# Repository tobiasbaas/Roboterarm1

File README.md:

# Konzeption und Realisierung eines Edge-KI-Systems zur visuellen Posenschätzung eines Roboterarms

Herzlich willkommen zum Repo des Robotersarmes der Arbeitsgruppe. Bitte beachtet, dass es sich hierbei handelt 
um eine Erweiterung bereits vorhandener Infrastruktur. Für mehr Infos siehe das bisherige Github Repo:
- (https://github.com/mama1120/rpi_ros_can_module.git)

Sowie als auch das offiziele Wiki zu den vergangegen Projekten im Ilias:
- (https://ilias.h-ka.de/goto.php?target=wiki_787531#il_mhead_t_focus)

<br>

>In dieser Readme wird der Gesamte Aufbau des Roboterarmes inklusive der Erweiterung, die im Rahmen der 
>Bachelorthesis durchgeführt wurden, erläutert. Es soll einen Schnelleinstieg ermöglichen, indem ihr den 
>Roboter mithilfe des RaspberryPI, STM32N6 Board und eurem Laptop bewegen könnt. Für tieferes Verständis
>des Projektes navigiert in die Unterordner des Repo.

---

## 1. Systemübersicht

Drei Geräte arbeiten zusammen. Der Laptop ist der Taktgeber, er steuert den Roboter und
löst die Bildaufnahme aus.

```
        ┌──────────────────────────────┐
        │  Laptop (Windows)            │
        │  capture_image.py            │
        └───────┬──────────────┬───────┘
                │              │
   UDP (WLAN)   │              │  USB CDC (virtueller COM-Port)
   4x float32   │              │  Kommandos: PING / TEST / CAPTURE
   Winkel [rad] │              │  Antwort: Bild 640x480 RGB565
                ▼              ▼
   ┌───────────────────┐   ┌──────────────────────────┐
   │ Raspberry Pi      │   │ STM32N6570-DK            │
   │ ROS2 + UDP-Bridge │   │ Kamera IMX335 + NPU      │
   │ CAN-Bus           │   │ Live-Bild auf LCD        │
   └────────┬──────────┘   └──────────────────────────┘
            │ CAN
            ▼
     ┌──────────────┐
     │ Roboterarm   │   Open-Loop, 4 Gelenke, keine Encoder
     └──────────────┘
```

**Warum dieser Aufbau?**
Der Roboterarm ist ein Open-Loop-System, es gibt keine Rotary-Encoder oder Hallsensoren,
die den tatsächlichen Winkel zurückmelden. Für das KI-Training muss aber jedes Bild exakt
zu einem bekannten Winkelsatz gehören. Deshalb wird der Roboter nicht über RViz von Hand
bewegt, sondern von einem eigenen Python-Skript auf eine bekannte Zielpose gefahren.
Das Skript wartet, bis die Bewegung sicher abgeschlossen ist, löst dann die Bildaufnahme
aus und schreibt Bild und Winkel gemeinsam in eine CSV-Datei. Eine korrekt angefahrene
Nullposition ist dabei die Grundvoraussetzung.

---

## 2. Repository-Struktur

```
.
├── 02_Software/
│   ├── Beachlor_Thesis_AI/     # KI-Pipeline (Training, Datenaufbereitung, Export)
│   ├── Image_Capture_Python/   # Host-Skripte: Trainingsdatenaufnahme (nur zusammen mit STM)
│   ├── New_Image_Capture/      # STM32-Firmware: Trainingsdatenaufnahme (Echte Bilder)
│   └── Thesis_Robot_Pose/      # STM32-Firmware: zusätzlich KI-Inferenz auf der NPU
├── 03_Hardware/
│   ├── STM32N6_Thesis_Board/   # Eigenes KiCad-Board (STM32N657X0H3Q)
│   └── Nucleo_PCB_FIles/       # Altium-Daten des MB1940-Referenzdesigns
└── README.md                   # diese Datei
```

## 3. Schellstart

### 3.1 Voraussetzungen

**Hardware**

| Komponente | Anmerkung |
|---|---|
| Roboterarm mit CAN-Anbindung | 4 angesteuerte Gelenke |
| Raspberry Pi | ROS2 im Docker-Image, CAN-HAT |
| STM32N6570-DK | Kamera IMX335, LCD RK050HR18 |
| Laptop | Windows, MAC |

> [!IMPORTANT]
>Bittet achtet darauf, dass euer Laptop und der Raspberry im selben Netzwerk miteinander verbunden sind!

<br>

**Software auf dem Laptop**

Falls ihr noch kein Python auf euren Laptop verwendet habt, so installiert zuerst **Miniconda**
(https://www.anaconda.com/download/success) und erstellt ein Custom Environment für 
dieses Projekt. 

Dazu öffnet ihr das **Anaconda Powershell** und gibt folgenden Commands **nacheinander**
in das Terminal ein:

```bash
conda create --name Euer_Env_Name python=3.14
```

```bash
conda activate Euer_Env_Name
```

```bash
pip install ultralytics==8.4.146 torch==2.14.0 onnx==1.22.0 onnxruntime==1.29.0 opencv-python==5.0.0.93 numpy==2.4.6 pillow==12.3.0 pandas==3.0.5 matplotlib==3.11.1 pyserial==3.5 notebook==7.6.2 label-studio==1.23.0
```

Zusätzlich benötigt ihr für die Inbetriebnahme des STM32N6 Boards die folgende Software 
von ST-Microelectronics:

- STM32 VsCode Extension  (https://www.st.com/content/st_com/en/campaigns/stm32-vs-code-extension-z11.html)
- STM32 Cube CLT          (https://www.st.com/en/development-tools/stm32cubeclt.html)
- STM32 Cube Programmer   (https://www.st.com/en/development-tools/stm32cubeprog.html)
- STM32Cube AI Studio     (https://www.st.com/content/st_com/en/campaigns/edge-ai-toolchain-for-mcus-z14.html)

### 3.2 Schritt 1: Roboter am Raspberry Pi starten

> [!IMPORTANT]
> Das **Passwort** für den Pi selber und der Ausführung des Codes lautet: **`ubuntu`**.

Auf dem Raspberry Pi genügt **ein Terminal und ein Befehl**. Alle Docker-Workspaces
werden dabei im Hintergrund initialisiert:

```bash
./boot_robot.sh
```

Damit werden gestartet:

* CAN-Bus
* ROS2 inklusive aktiver UDP-Bridge
  
Nachdem alles initialisiert hat, kann der Roboter bereits gesteuert werden über RViz. Für mehr Infos zum 
starten von RViz, schaut im oben verlinkten GitHub Repo nach.<br>

Optional, um die CAN-Nachrichten live mitzulesen (zweites Terminal, erst nach dem
Start des Roboters):

```bash
candump can0
```
> [!IMPORTANT]
> Den Roboter niemals gleichzeitig über RViz und über das Python-Skript
> ansprechen. 

### 3.3 Schritt 2: STM32N6570-DK vorbereiten

1. Boot-Pins **BOOT0 und BOOT1 auf Low** setzen (Flash-Mode, bevorzugte Betriebsart).
2. FSBL und Appli in der CubeIDE bauen.
3. Beide `.bin`-Dateien signieren, siehe [Abschnitt 4](#4-firmware-flashen-signierung).
4. External Flash löschen, dann **erst FSBL, danach Appli** flashen.
5. Board per USB an den Laptop stecken. Es meldet sich als virtueller COM-Port und sendet
   nach der Enumeration dreimal `READY`.

Für die reine Datenaufnahme wird `02_Software/New_Image_Capture` geflasht.

### 3.4 Schritt 3: Bildaufnahme starten

In `02_Software/Image_Capture_Python/capture_image.py` oben die Konfiguration prüfen:

```python
COM_PORT = "COM4"              # COM-Port des STM32 im Gerätemanager nachsehen
UDP_IP   = "192.168.4.152"     # IP des Raspberry Pi
UDP_PORT = 5005
num_positions = 1000           # Anzahl aufzunehmender Posen
```

Dann starten:

```bash
cd 02_Software/Image_Capture_Python
python capture_image.py
```

Ablauf pro Bild: Zielpose per UDP senden, 4 s warten, `CAPTURE` über USB senden,
Bild empfangen, als PNG speichern, Zeile in `labels.csv` schreiben.

Ergebnis liegt in `dataset/images/<lauf_zeitstempel>/pose_XXXX.png` plus `dataset/labels.csv`.

---

## 4. Firmware flashen: Signierung

Der STM32N6 führt nur signierte Images aus. FSBL und Appli müssen **getrennt** signiert
werden.
<br><br>

> [!IMPORTANT]
>Das Skript `sign_binaries.bat` im jeweiligen Firmware-Projekt automatisiert die folgenden Schritte.

<br>
1. In der CubeIDE beide Umgebungen bauen. Die `.bin` liegt im `Debug`-Ordner des jeweiligen
   Projekts.
2. Eingabeaufforderung öffnen und in dieses Verzeichnis wechseln:

   ```bat
   cd /d <Pfad zum Debug-Ordner>
   ```

3. Signieren:

   ```bat
   STM32_SigningTool_CLI.exe -bin <name>.bin -t fsbl -la 0x80000000 -hv 2.3 -nk -o <name>-trusted.bin -align -dump <name>-trusted.bin
   ```

   Das Ergebnis der Signierung steht **ganz oben** in der Ausgabe, nicht am Ende.
4. Die entstandene `*-trusted.bin` mit dem STM32CubeProgrammer flashen.
   Reihenfolge: External Flash löschen, dann FSBL, dann Appli.

---

## 5. Schnittstellen im Detail

### 5.1 Laptop zu Raspberry Pi (UDP)

| Eigenschaft | Wert |
|---|---|
| Protokoll | UDP, unidirektional (Laptop sendet) |
| Ziel | `192.168.4.152:5005` |
| Nutzdaten | 4 x `float32`, Big-Endian (`struct` Format `!4f`) |
| Einheit | **Radiant**, Reihenfolge Joint 1 bis Joint 4 |
| Gelenkgrenzen | J1 -95° bis 95°, J2 0° bis 95°, J3 -80° bis 80°, J4 -10° bis 50° |

Vor dem Start fährt das Skript dreimal die Nullposition `[0,0,0,0]` an und wartet 4 s.

**Änderung am Raspberry Pi:** Die UDP-Bridge wurde in
`robot_moveit_config/launch/planning_execution.launch.py` ergänzt. Die betroffenen Stellen
sind in der Datei markiert, weitere Anpassungen sind für Folgeprojekte nicht nötig.
Aktiviert wird sie über den Launch-Parameter:

```bash
ros2 launch robot_moveit_config planning_execution.launch.py use_udp_bridge:=true
```

`boot_robot.sh` setzt diesen Parameter bereits. Der normale ROS2-Workflow bleibt
unverändert, RViz funktioniert weiterhin (aber nicht gleichzeitig, siehe Warnung oben).

---

## 6. Troubleshooting

| Symptom | Ursache und Abhilfe |
|---|---|
| `capture_image.py` bleibt bei "Warte auf Lebenszeichen" | Board sendet kein `READY`. Board resetten, COM-Port im Gerätemanager prüfen, ggf. Firmware nicht korrekt geflasht |
| Roboter reagiert nicht auf UDP | `boot_robot.sh` gestartet? UDP-Bridge aktiv? Laptop und Pi im selben WLAN? IP in `capture_image.py` korrekt? |
| Roboter fährt ruckartig oder unvorhersehbar | RViz läuft parallel. Nur eine Steuerquelle gleichzeitig verwenden |
| Bilder und Winkel passen nicht zusammen | Nullposition nicht korrekt angefahren, oder Wartezeit nach der Bewegung zu kurz |
| Board startet nach dem Flashen nicht | Signierung fehlt oder falsche Reihenfolge. External Flash löschen, erst FSBL, dann Appli |
| Bild kommt unvollständig an | `CAPTURE_TIMEOUT` erhöhen, anderes USB-Kabel oder anderen Port verwenden |

---

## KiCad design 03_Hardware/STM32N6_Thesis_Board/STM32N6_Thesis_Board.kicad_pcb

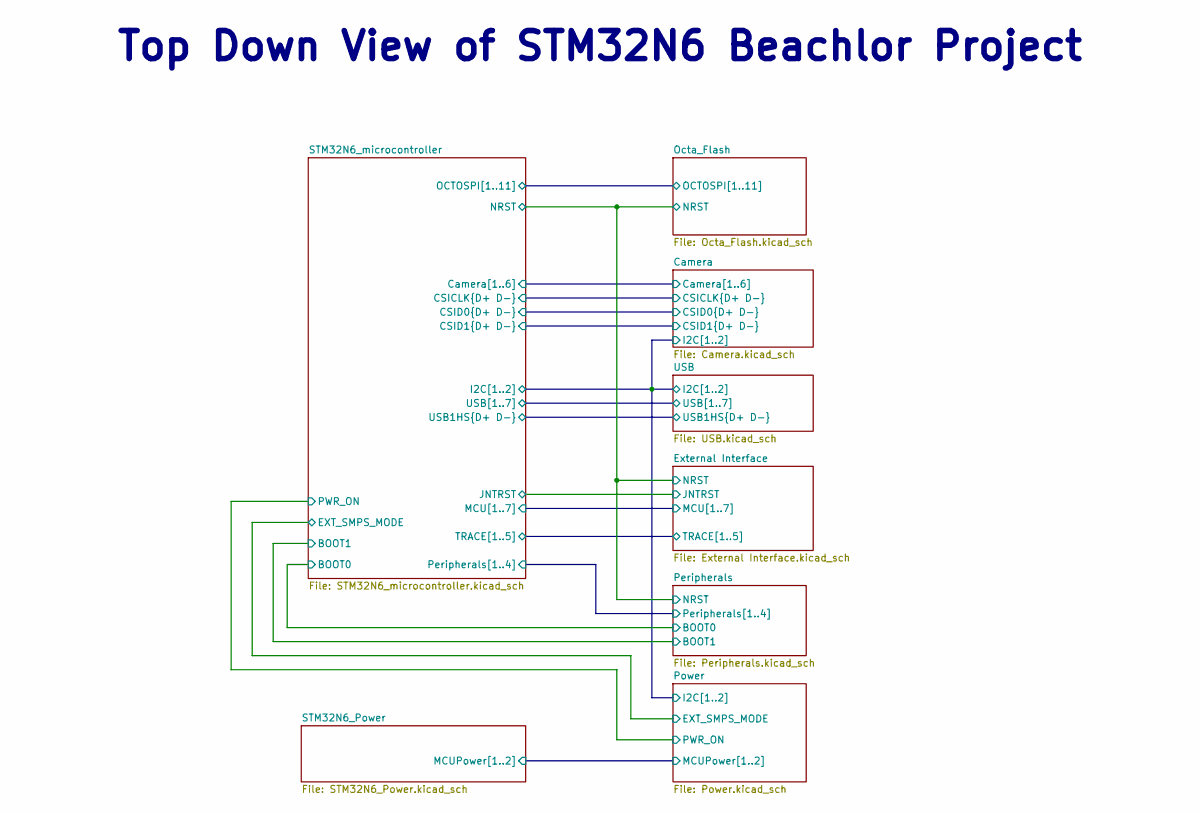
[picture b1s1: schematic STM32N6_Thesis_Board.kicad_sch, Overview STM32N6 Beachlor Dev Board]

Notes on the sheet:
Top Down View of STM32N6 Beachlor Project

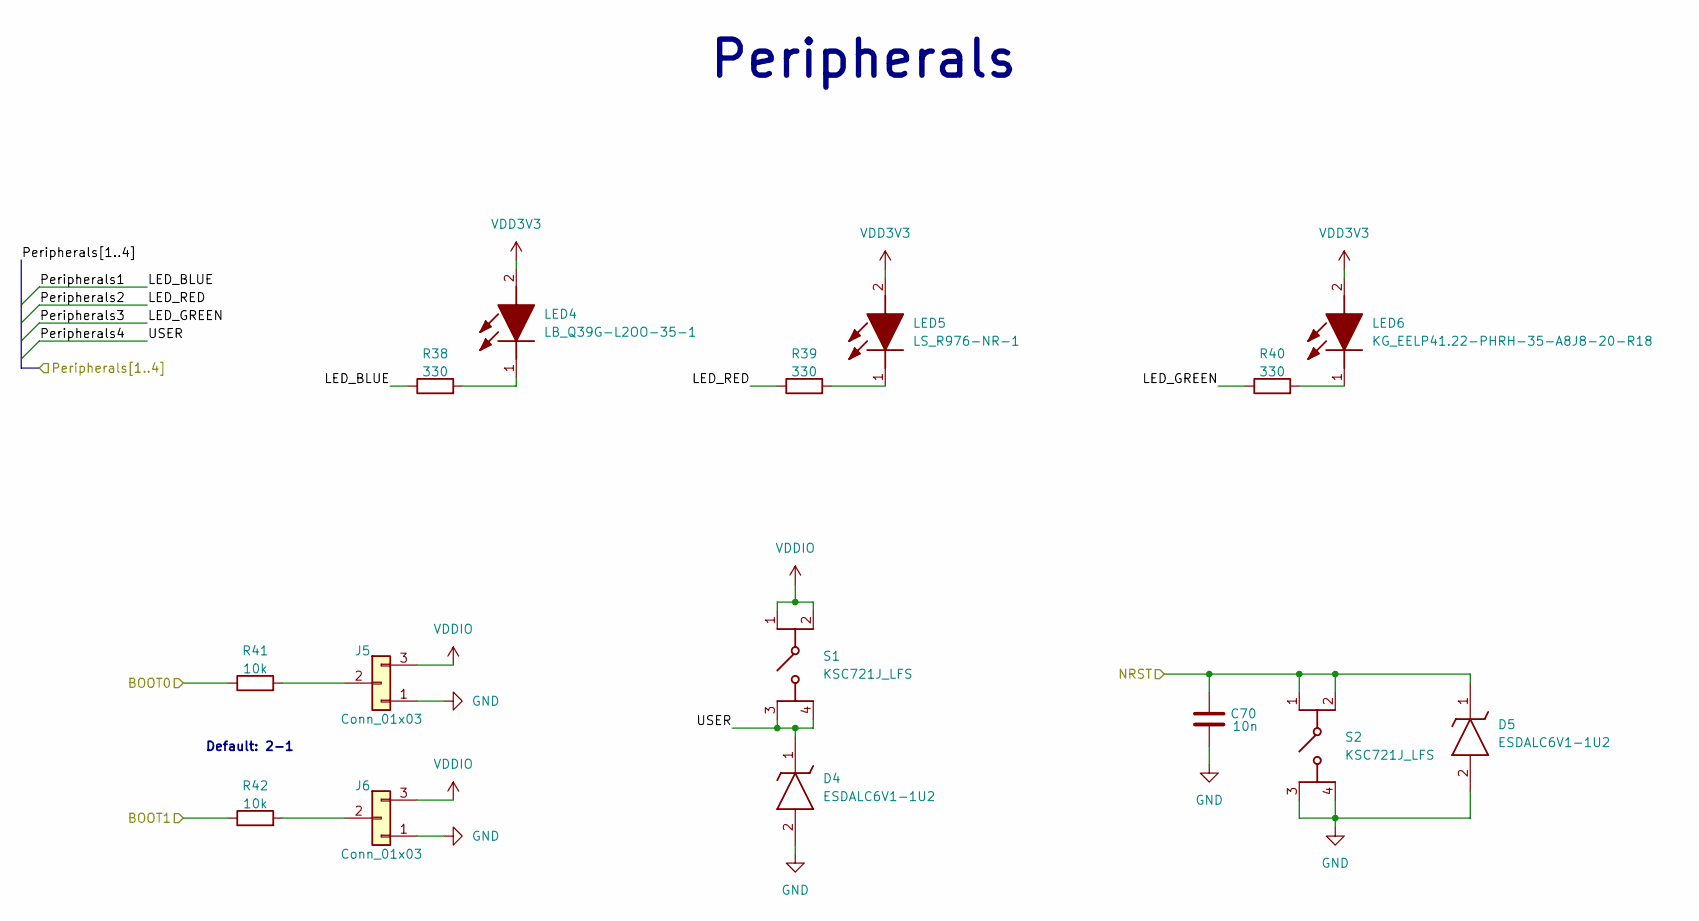
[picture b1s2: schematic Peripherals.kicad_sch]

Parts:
C70: 10n; C_0603_1608Metric
D4, D5: ESDALC6V1-1U2; ESDALC6V11U2; Mouser Part Number 511-ESDALC6V1-1U2
J5, J6: Conn_01x03; PinHeader_1x03_P2.54mm_Vertical
LED4: LB_Q39G-L2OO-35-1; LEDC1608X40N; Mouser Part Number 720-LBQ39GL2N2351
LED5: LS_R976-NR-1; LEDC2012X40N; Mouser Part Number 720-LSR976-NR-1
LED6: KG_EELP41.22-PHRH-35-A8J8-20-R18; KGEELP4122PHRH35A8J820R18; Mouser Part Number 720-P4122PHRH35A8J82
R38, R39, R40: 330; R_0603_1608Metric
R41, R42: 10k; R_0603_1608Metric
S1, S2: KSC721J_LFS; KSC721JLFS; Mouser Part Number 611-KSC721JLFS

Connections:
/External Interface/NRST: C70.2, D5.1 (K), S2.1 (COM_1), S2.2 (COM_2); also elsewhere on the board
/Peripherals/BOOT0: R41.1; also elsewhere on the board
/Peripherals/Peripherals1: R38.1; also elsewhere on the board
/Peripherals/Peripherals2: R39.1; also elsewhere on the board
/Peripherals/Peripherals3: R40.1; also elsewhere on the board
/Peripherals/Peripherals4: D4.1 (K), S1.3 (NO_1), S1.4 (NO_2); also elsewhere on the board
/STM32N6_microcontroller/BOOT1: R42.1; also elsewhere on the board
GND: C70.1, D4.2 (A), D5.2 (A), J5.1, J6.1, S2.3 (NO_1), S2.4 (NO_2); also elsewhere on the board
unnamed: J5.2, R41.2
unnamed: J6.2, R42.2
unnamed: LED4.1 (K), R38.2
unnamed: LED5.1 (K), R39.2
unnamed: LED6.1 (K), R40.2
VDD3V3: LED4.2 (A), LED5.2 (A), LED6.2 (A); also elsewhere on the board
VDDIO: J5.3, J6.3, S1.1 (COM_1), S1.2 (COM_2); also elsewhere on the board

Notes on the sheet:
Peripherals
Default: 2-1

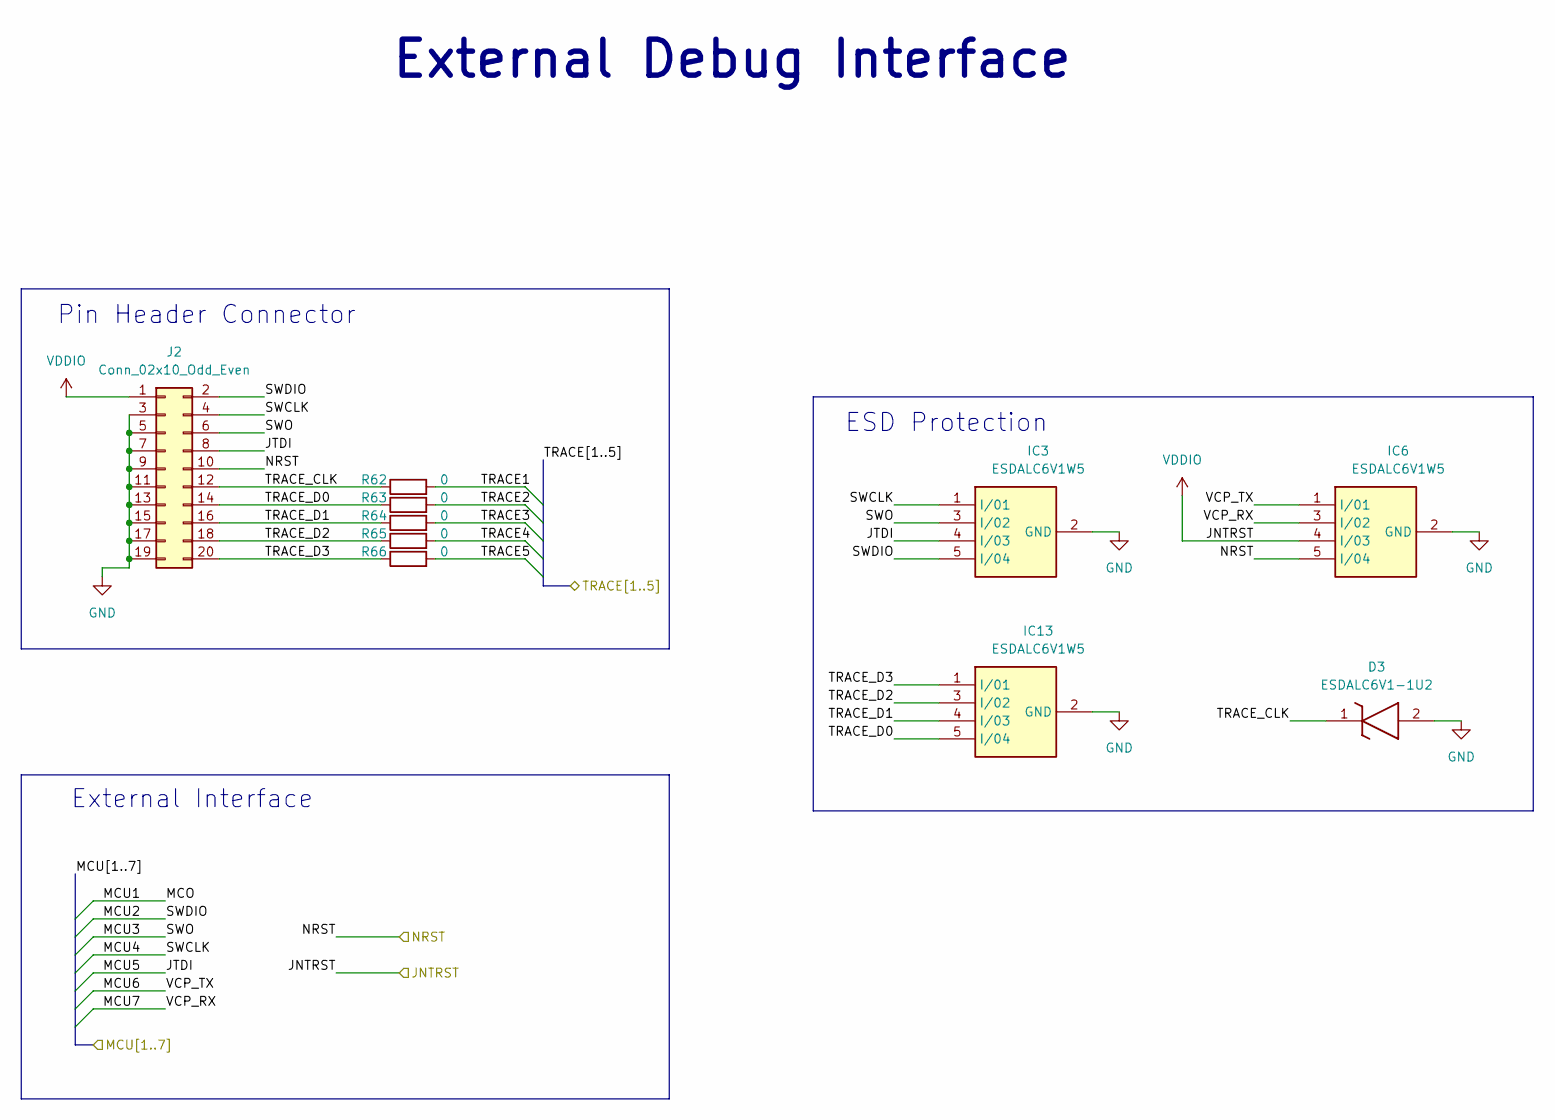
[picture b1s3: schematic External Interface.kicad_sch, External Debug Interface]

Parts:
D3: ESDALC6V1-1U2; ESDALC6V11U2; Mouser Part Number 511-ESDALC6V1-1U2
IC3, IC6, IC13: ESDALC6V1W5; SOT65P210X110-5N; Mouser Part Number 511-ESDALC6V1W5
J2: Conn_02x10_Odd_Even; PinHeader_2x10_P2.54mm_Vertical
R62, R63, R64, R65, R66: 0; R_0603_1608Metric

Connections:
/External Interface/MCU2: IC3.5 (I/04), J2.2; also elsewhere on the board
/External Interface/MCU3: IC3.3 (I/02), J2.6; also elsewhere on the board
/External Interface/MCU4: IC3.1 (I/01), J2.4; also elsewhere on the board
/External Interface/MCU5: IC3.4 (I/03), J2.8; also elsewhere on the board
/External Interface/MCU6: IC6.1 (I/01); also elsewhere on the board
/External Interface/MCU7: IC6.3 (I/02); also elsewhere on the board
/External Interface/NRST: IC6.5 (I/04), J2.10; also elsewhere on the board
/External Interface/TRACE1: R62.2; also elsewhere on the board
/External Interface/TRACE2: R63.2; also elsewhere on the board
/External Interface/TRACE3: R64.2; also elsewhere on the board
/External Interface/TRACE4: R65.2; also elsewhere on the board
/External Interface/TRACE5: R66.2; also elsewhere on the board
/External Interface/TRACE_CLK: D3.1 (K), J2.12, R62.1
/External Interface/TRACE_D0: IC13.5 (I/04), J2.14, R63.1
/External Interface/TRACE_D1: IC13.4 (I/03), J2.16, R64.1
/External Interface/TRACE_D2: IC13.3 (I/02), J2.18, R65.1
/External Interface/TRACE_D3: IC13.1 (I/01), J2.20, R66.1
GND: D3.2 (A), IC3.2 (GND), IC6.2 (GND), IC13.2 (GND), J2.3, J2.5, J2.7, J2.9, J2.11, J2.13, J2.15, J2.17, J2.19; also elsewhere on the board
VDDIO: IC6.4 (I/03), J2.1; also elsewhere on the board

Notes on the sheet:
External Debug Interface
External Interface
Pin Header Connector
ESD Protection

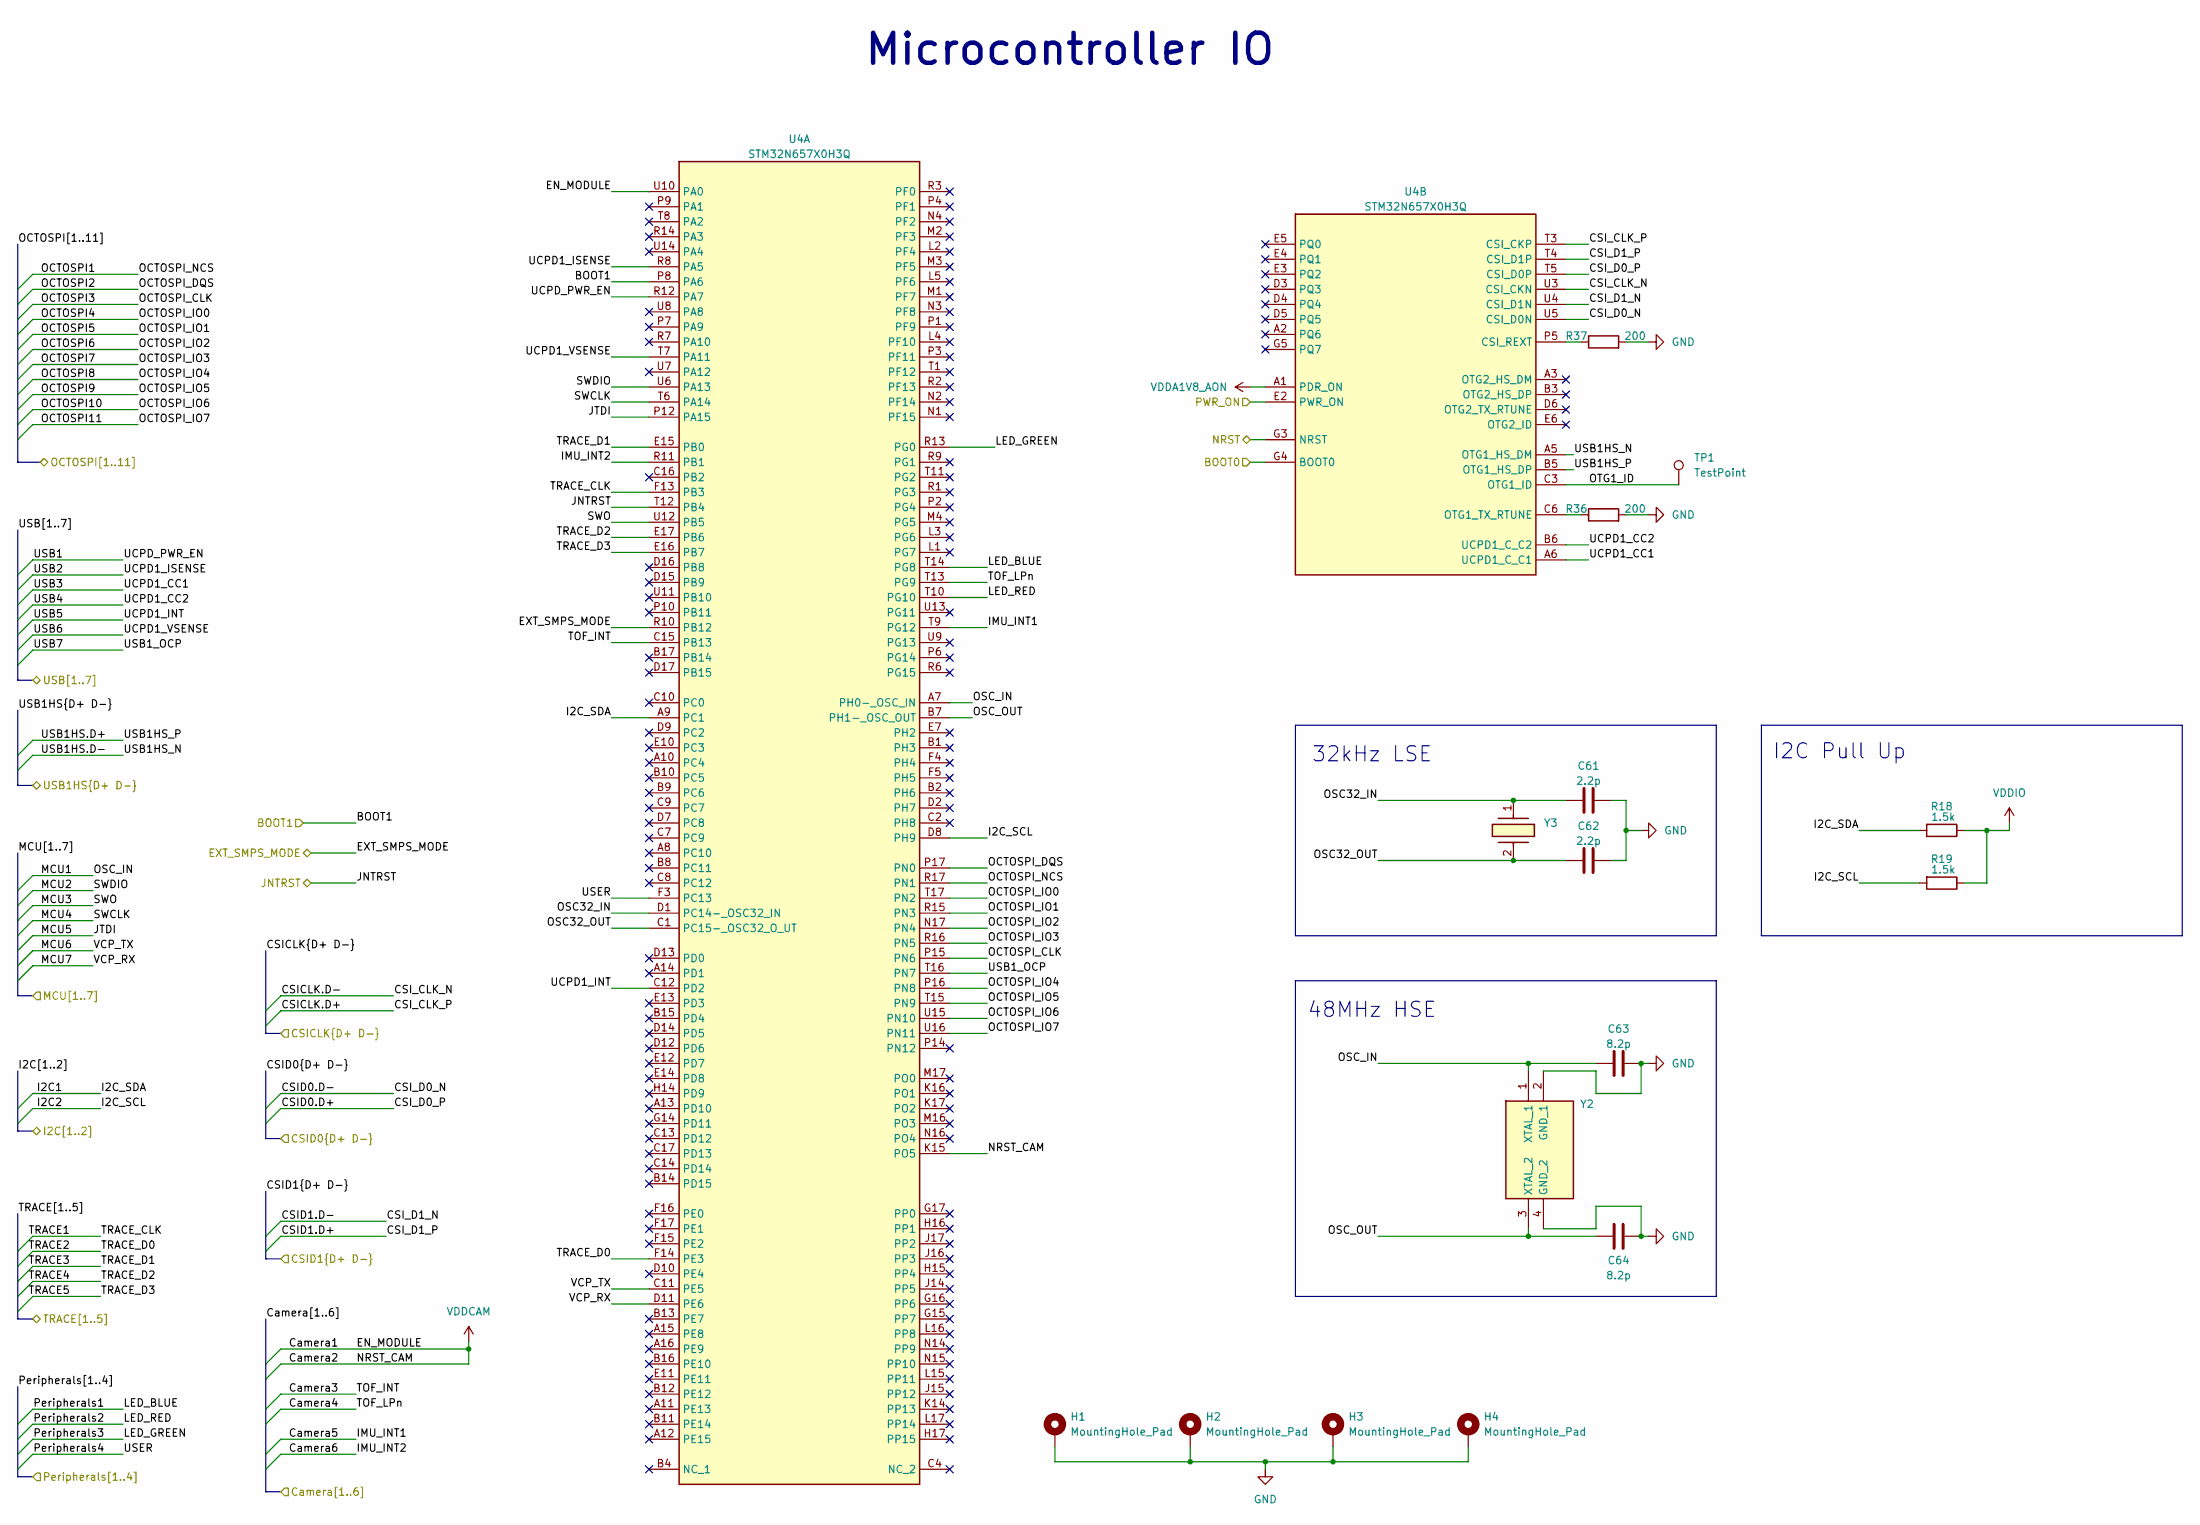
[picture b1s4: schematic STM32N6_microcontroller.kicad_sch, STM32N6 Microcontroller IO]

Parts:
C61, C62: 2.2p; C_0603_1608Metric
C63, C64: 8.2p; C_0603_1608Metric
H1, H2, H3, H4: MountingHole_Pad; MountingHole_3.2mm_M3_Pad_Via
R18, R19: 1.5k; R_0603_1608Metric
R36, R37: 200; R_0603_1608Metric
TP1: TestPoint
U4: STM32N657X0H3Q; BGA264C80P17X17_1400X1400X100; Mouser Part Number 511-STM32N657X0H3Q
Y2: ABM12W-48.0000MHZ-7-D1X-T3; ABM12W300000MHZ6B1UT3; Mouser Part Number 815-12W48-7D1XT
Y3: CM7V-T1A-32.768KHZ-6PF-20PPM-TA-QC; CM7V32768TBQA020; Mouser Part Number 428-201843-MG01

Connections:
/Camera/CSICLK.D+: U4.T3 (CSI_CKP); also elsewhere on the board
/Camera/CSICLK.D-: U4.U3 (CSI_CKN); also elsewhere on the board
/Camera/CSID0.D+: U4.T5 (CSI_D0P); also elsewhere on the board
/Camera/CSID0.D-: U4.U5 (CSI_D0N); also elsewhere on the board
/Camera/CSID1.D+: U4.T4 (CSI_D1P); also elsewhere on the board
/Camera/CSID1.D-: U4.U4 (CSI_D1N); also elsewhere on the board
/Camera/Camera3: U4.C15 (PB13); also elsewhere on the board
/Camera/Camera4: U4.T13 (PG9); also elsewhere on the board
/Camera/Camera5: U4.T9 (PG12); also elsewhere on the board
/Camera/Camera6: U4.R11 (PB1); also elsewhere on the board
/Camera/I2C1: R18.2, U4.A9 (PC1); also elsewhere on the board
/Camera/I2C2: R19.2, U4.D8 (PH9); also elsewhere on the board
/External Interface/MCU1: C63.1, U4.A7 (PH0-_OSC_IN), Y2.1 (XTAL_1)
/External Interface/MCU2: U4.U6 (PA13); also elsewhere on the board
/External Interface/MCU3: U4.U12 (PB5); also elsewhere on the board
/External Interface/MCU4: U4.T6 (PA14); also elsewhere on the board
/External Interface/MCU5: U4.P12 (PA15); also elsewhere on the board
/External Interface/MCU6: U4.C11 (PE5); also elsewhere on the board
/External Interface/MCU7: U4.D11 (PE6); also elsewhere on the board
/External Interface/NRST: U4.G3 (NRST); also elsewhere on the board
/External Interface/TRACE1: U4.F13 (PB3); also elsewhere on the board
/External Interface/TRACE2: U4.F14 (PE3); also elsewhere on the board
/External Interface/TRACE3: U4.E15 (PB0); also elsewhere on the board
/External Interface/TRACE4: U4.E17 (PB6); also elsewhere on the board
/External Interface/TRACE5: U4.E16 (PB7); also elsewhere on the board
/Octa_Flash/OCTOSPI1: U4.R17 (PN1); also elsewhere on the board
/Octa_Flash/OCTOSPI2: U4.P17 (PN0); also elsewhere on the board
/Octa_Flash/OCTOSPI3: U4.P15 (PN6); also elsewhere on the board
/Octa_Flash/OCTOSPI4: U4.T17 (PN2); also elsewhere on the board
/Octa_Flash/OCTOSPI5: U4.R15 (PN3); also elsewhere on the board
/Octa_Flash/OCTOSPI6: U4.N17 (PN4); also elsewhere on the board
/Octa_Flash/OCTOSPI7: U4.R16 (PN5); also elsewhere on the board
/Octa_Flash/OCTOSPI8: U4.P16 (PN8); also elsewhere on the board
/Octa_Flash/OCTOSPI9: U4.T15 (PN9); also elsewhere on the board
/Octa_Flash/OCTOSPI10: U4.U15 (PN10); also elsewhere on the board
/Octa_Flash/OCTOSPI11: U4.U16 (PN11); also elsewhere on the board
/Peripherals/BOOT0: U4.G4 (BOOT0); also elsewhere on the board
/Peripherals/Peripherals1: U4.T14 (PG8); also elsewhere on the board
/Peripherals/Peripherals2: U4.T10 (PG10); also elsewhere on the board
/Peripherals/Peripherals3: U4.R13 (PG0); also elsewhere on the board
/Peripherals/Peripherals4: U4.F3 (PC13); also elsewhere on the board
/Power/PWR_LP: U4.R10 (PB12); also elsewhere on the board
/Power/PWR_ON: U4.E2 (PWR_ON); also elsewhere on the board
/STM32N6_microcontroller/BOOT1: U4.P8 (PA6); also elsewhere on the board
/STM32N6_microcontroller/OSC32_IN: C61.1, U4.D1 (PC14-_OSC32_IN), Y3.1
/STM32N6_microcontroller/OSC32_OUT: C62.1, U4.C1 (PC15-_OSC32_O_UT), Y3.2
/STM32N6_microcontroller/OSC_OUT: C64.1, U4.B7 (PH1-_OSC_OUT), Y2.3 (XTAL_2)
/STM32N6_microcontroller/OTG1_ID: TP1.1, U4.C3 (OTG1_ID)
/STM32N6_microcontroller/USB1: U4.R12 (PA7); also elsewhere on the board
/STM32N6_microcontroller/USB1HS.D+: U4.B5 (OTG1_HS_DP); also elsewhere on the board
/STM32N6_microcontroller/USB1HS.D-: U4.A5 (OTG1_HS_DM); also elsewhere on the board
/STM32N6_microcontroller/USB2: U4.R8 (PA5); also elsewhere on the board
/STM32N6_microcontroller/USB3: U4.A6 (UCPD1_C_C1); also elsewhere on the board
/STM32N6_microcontroller/USB4: U4.B6 (UCPD1_C_C2); also elsewhere on the board
/STM32N6_microcontroller/USB5: U4.C12 (PD2); also elsewhere on the board
/STM32N6_microcontroller/USB6: U4.T7 (PA11); also elsewhere on the board
/STM32N6_microcontroller/USB7: U4.T16 (PN7); also elsewhere on the board
GND: C61.2, C62.2, C63.2, C64.2, H1.1, H2.1, H3.1, H4.1, R36.2, R37.2, Y2.2 (GND_1), Y2.4 (GND_2); also elsewhere on the board
unnamed: R37.1, U4.P5 (CSI_REXT)
unnamed: R36.1, U4.C6 (OTG1_TX_RTUNE)
VDDA1V8_AON: U4.A1 (PDR_ON); also elsewhere on the board
VDDCAM: U4.K15 (PO5), U4.U10 (PA0); also elsewhere on the board
VDDIO: R18.1, R19.1, U4.T12 (PB4); also elsewhere on the board

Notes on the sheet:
32kHz LSE
I2C Pull Up
Microcontroller IO
48MHz HSE

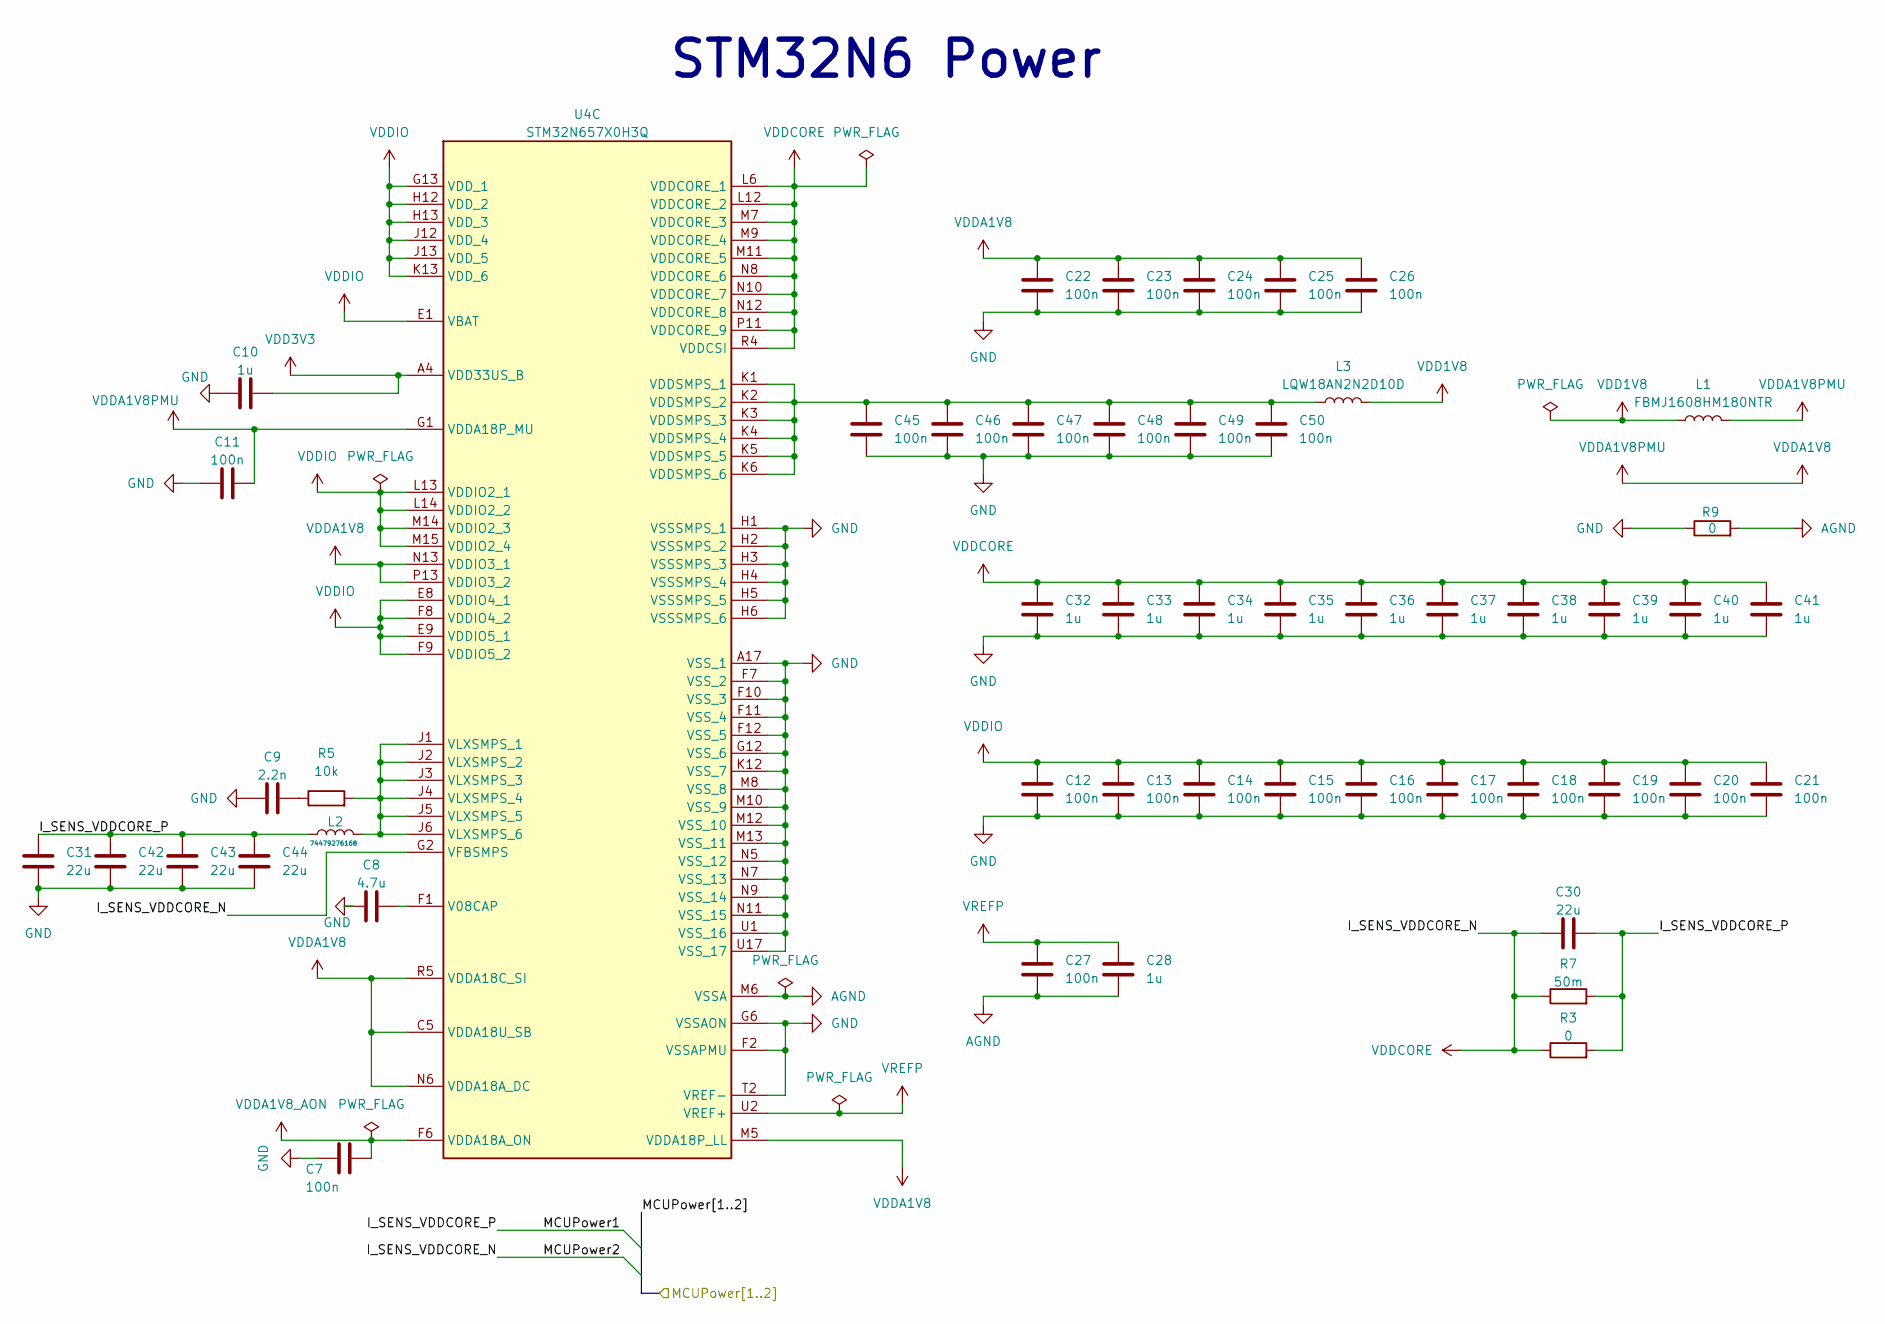
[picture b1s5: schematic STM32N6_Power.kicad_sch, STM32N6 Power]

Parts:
C7, C11, C12, C13, C14, C15, C16, C17, C18, C19, C20, C21, C22, C23, C24, C25, C26, C27, C45, C46, C47, C48, C49, C50: 100n; C_0201_0603Metric
C8: 4.7u; C_0201_0603Metric
C9: 2.2n; C_0201_0603Metric
C10, C28, C32, C33, C34, C35, C36, C37, C38, C39, C40, C41: 1u; C_0201_0603Metric
C30, C31, C42, C43, C44: 22u; C_0402_1005Metric
L1: FBMJ1608HM180NTR; L_0603_1608Metric
L2: 74479276168; L_0805_2012Metric
L3: LQW18AN2N2D10D; L_0603_1608Metric
R3: 0; R_0402_1005Metric
R5: 10k; R_0603_1608Metric
R7: 50m; R_0402_1005Metric
R9: 0; R_0603_1608Metric
U4: STM32N657X0H3Q; BGA264C80P17X17_1400X1400X100; Mouser Part Number 511-STM32N657X0H3Q

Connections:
/Power/MCUPower1: C30.2, C31.1, C42.1, C43.1, C44.1, L2.1, R3.2, R7.2; also elsewhere on the board
AGND: C27.2, C28.2, R9.2, U4.M6 (VSSA)
GND: C7.2, C8.1, C9.1, C10.1, C11.1, C12.2, C13.2, C14.2, C15.2, C16.2, C17.2, C18.2, C19.2, C20.2, C21.2, C22.2, C23.2, C24.2, C25.2, C26.2, C31.2, C32.2, C33.2, C34.2, C35.2, C36.2, C37.2, C38.2, C39.2, C40.2, C41.2, C42.2, C43.2, C44.2, C45.2, C46.2, C47.2, C48.2, C49.2, C50.2, R9.1, U4.A17 (VSS_1), U4.F2 (VSSAPMU), U4.F7 (VSS_2), U4.F10 (VSS_3), U4.F11 (VSS_4), U4.F12 (VSS_5), U4.G6 (VSSAON), U4.G12 (VSS_6), U4.H1 (VSSSMPS_1), U4.H2 (VSSSMPS_2), U4.H3 (VSSSMPS_3), U4.H4 (VSSSMPS_4), U4.H5 (VSSSMPS_5), U4.H6 (VSSSMPS_6), U4.K12 (VSS_7), U4.M8 (VSS_8), U4.M10 (VSS_9), U4.M12 (VSS_10), U4.M13 (VSS_11), U4.N5 (VSS_12), U4.N7 (VSS_13), U4.N9 (VSS_14), U4.N11 (VSS_15), U4.T2 (VREF-), U4.U1 (VSS_16), U4.U17 (VSS_17); also elsewhere on the board
unnamed: C9.2, R5.1
unnamed: C8.2, U4.F1 (V08CAP)
unnamed: C45.1, C46.1, C47.1, C48.1, C49.1, C50.1, L3.1, U4.K1 (VDDSMPS_1), U4.K2 (VDDSMPS_2), U4.K3 (VDDSMPS_3), U4.K4 (VDDSMPS_4), U4.K5 (VDDSMPS_5), U4.K6 (VDDSMPS_6)
unnamed: L2.2, R5.2, U4.J1 (VLXSMPS_1), U4.J2 (VLXSMPS_2), U4.J3 (VLXSMPS_3), U4.J4 (VLXSMPS_4), U4.J5 (VLXSMPS_5), U4.J6 (VLXSMPS_6)
VDD1V8: L1.1, L3.2; also elsewhere on the board
VDD3V3: C10.2, U4.A4 (VDD33US_B); also elsewhere on the board
VDDA1V8: C11.2, C22.1, C23.1, C24.1, C25.1, C26.1, L1.2, U4.C5 (VDDA18U_SB), U4.G1 (VDDA18P_MU), U4.M5 (VDDA18P_LL), U4.N6 (VDDA18A_DC), U4.N13 (VDDIO3_1), U4.P13 (VDDIO3_2), U4.R5 (VDDA18C_SI); also elsewhere on the board
VDDA1V8_AON: C7.1, U4.F6 (VDDA18A_ON); also elsewhere on the board
VDDCORE: C30.1, C32.1, C33.1, C34.1, C35.1, C36.1, C37.1, C38.1, C39.1, C40.1, C41.1, R3.1, R7.1, U4.G2 (VFBSMPS), U4.L6 (VDDCORE_1), U4.L12 (VDDCORE_2), U4.M7 (VDDCORE_3), U4.M9 (VDDCORE_4), U4.M11 (VDDCORE_5), U4.N8 (VDDCORE_6), U4.N10 (VDDCORE_7), U4.N12 (VDDCORE_8), U4.P11 (VDDCORE_9), U4.R4 (VDDCSI); also elsewhere on the board
VDDIO: C12.1, C13.1, C14.1, C15.1, C16.1, C17.1, C18.1, C19.1, C20.1, C21.1, U4.E1 (VBAT), U4.E8 (VDDIO4_1), U4.E9 (VDDIO5_1), U4.F8 (VDDIO4_2), U4.F9 (VDDIO5_2), U4.G13 (VDD_1), U4.H12 (VDD_2), U4.H13 (VDD_3), U4.J12 (VDD_4), U4.J13 (VDD_5), U4.K13 (VDD_6), U4.L13 (VDDIO2_1), U4.L14 (VDDIO2_2), U4.M14 (VDDIO2_3), U4.M15 (VDDIO2_4); also elsewhere on the board
VREFP: C27.1, C28.1, U4.U2 (VREF+)

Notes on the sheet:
STM32N6 Power
